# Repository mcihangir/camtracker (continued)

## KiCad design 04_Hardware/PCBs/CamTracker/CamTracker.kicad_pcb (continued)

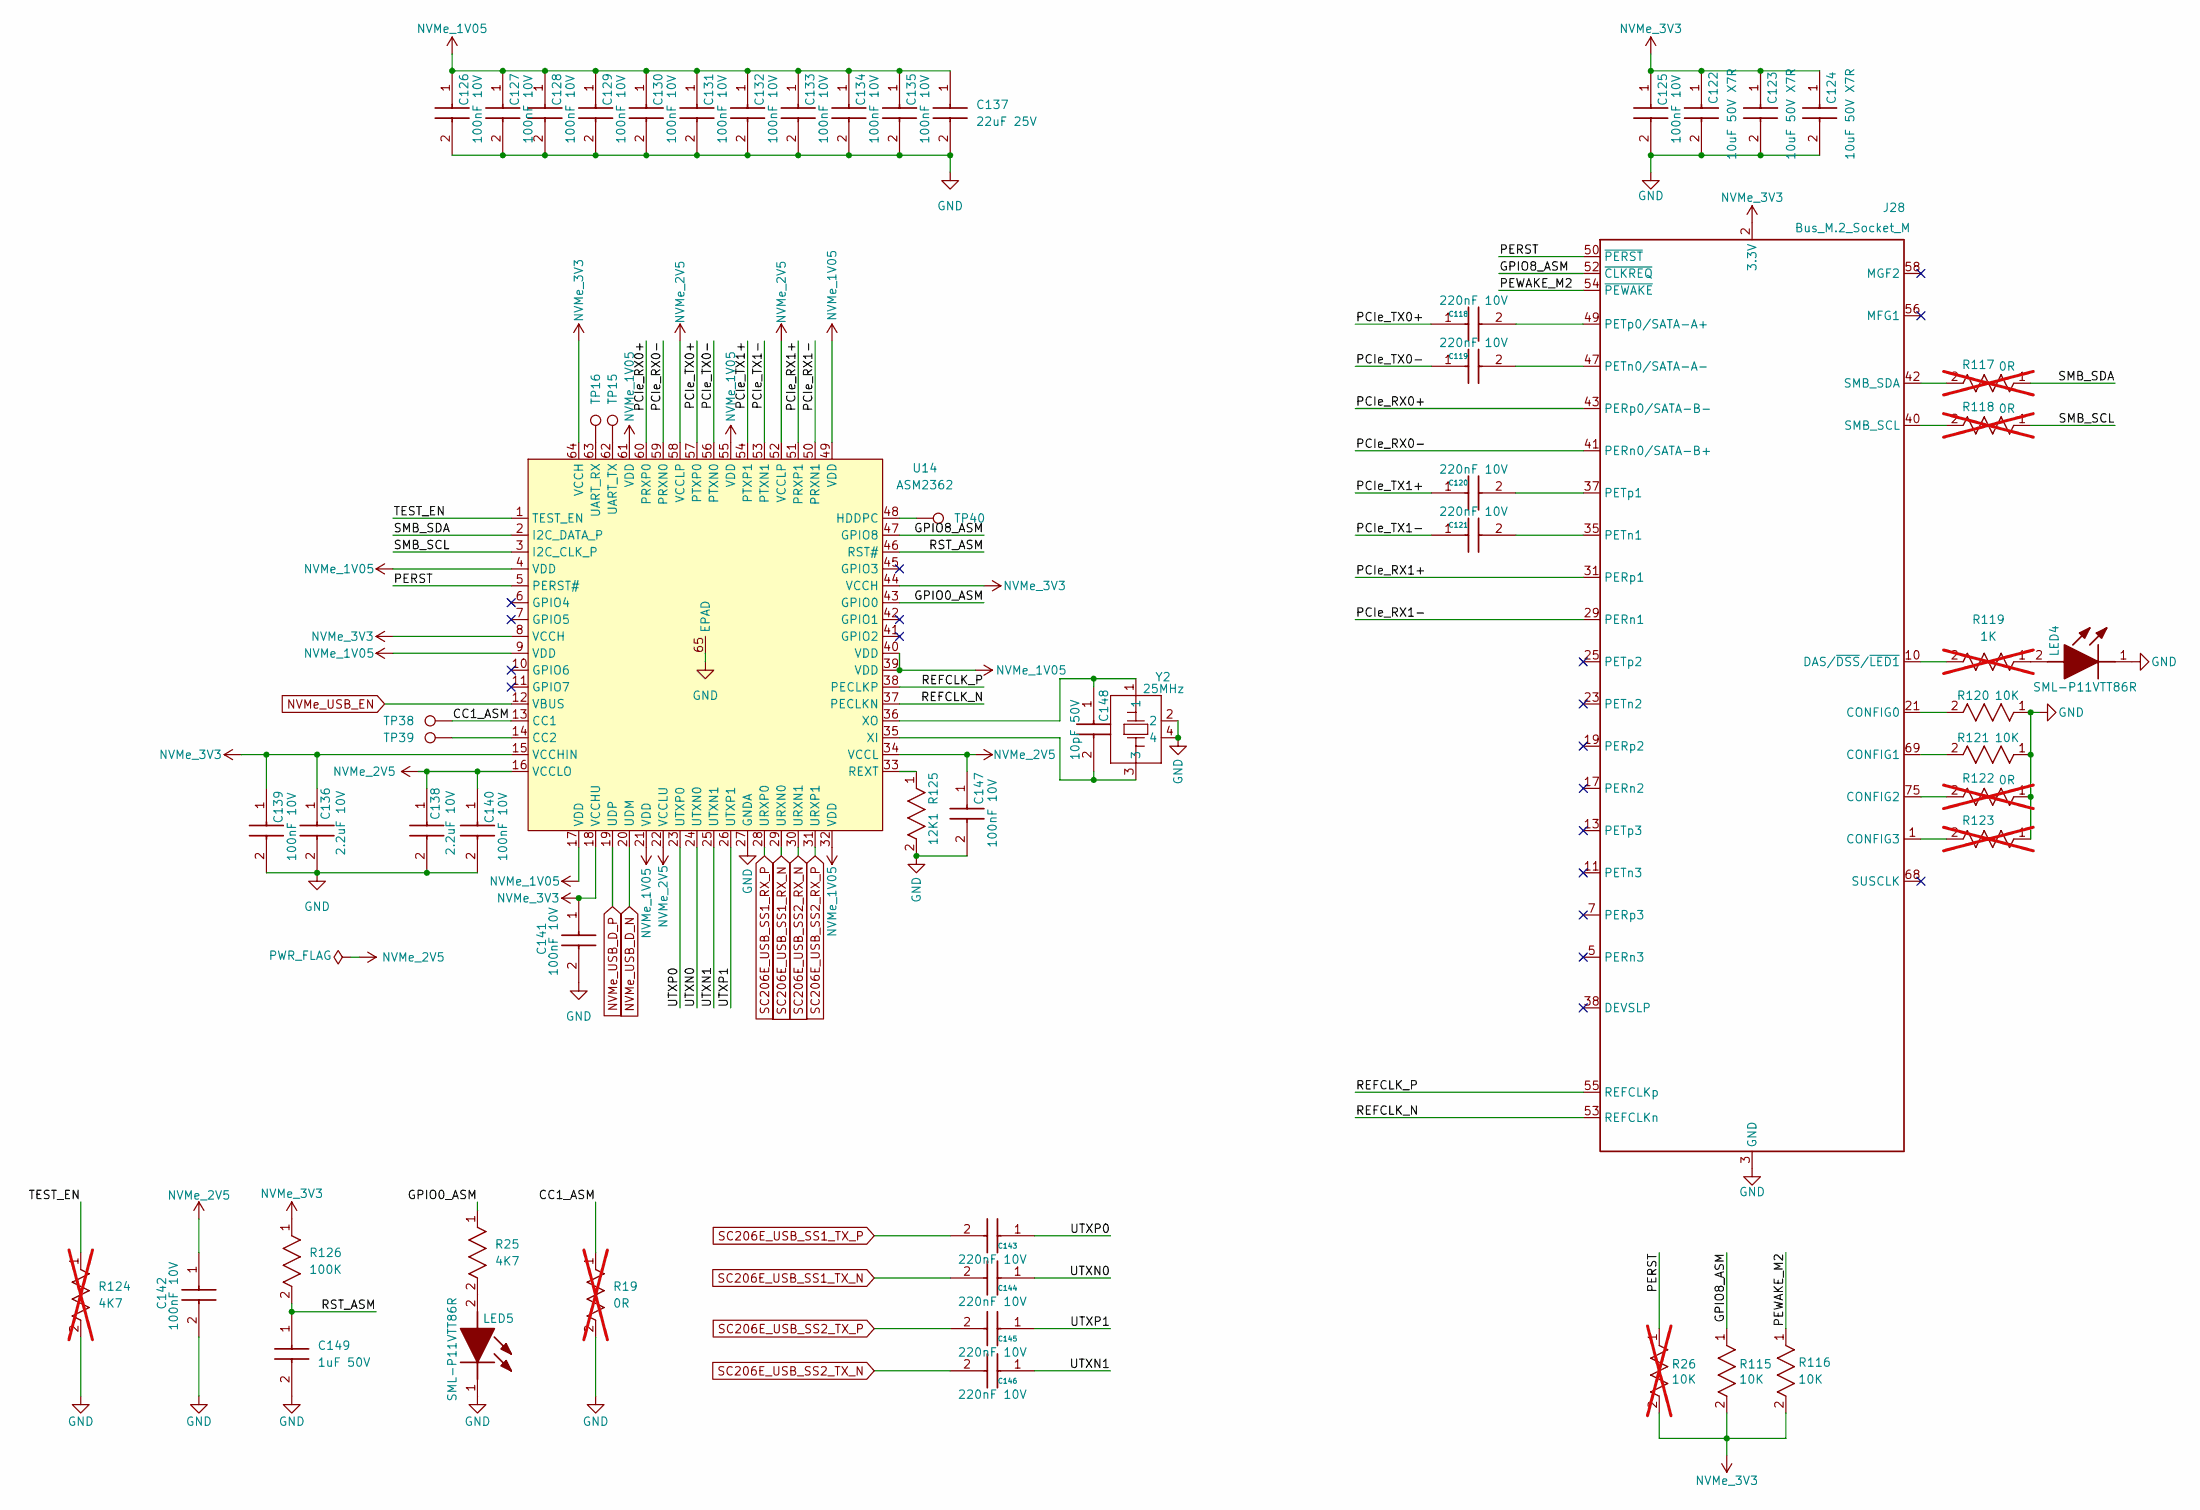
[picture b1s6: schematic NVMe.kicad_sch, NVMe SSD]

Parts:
C118, C119, C120, C121, C143, C144, C145, C146: 220nF 10V; CAPC1005X55N; Part Number GRM155R61A224JE19D
C122, C123, C124: 10uF 50V X7R; CAPC3216X190N; Part Number CL31B106KBK6PJE
C125, C126, C127, C128, C129, C130, C131, C132, C133, C134, C135, C139, C140, C141, C142, C147: 100nF 10V; CAPC1005X55N; Part Number GRM155R71A104KA01D
C136, C138: 2.2uF 10V; CAPC1608X90N; Part Number LMK107BJ225KA-T
C137: 22uF 25V; CAPC2012X145N; Part Number GRM21BR61E226ME44L
C148: 10pF 50V; CAPC1005X55N; Part Number GRM1555C1H100JA01D
C149: 1uF 50V; CAPC1005X55N; Part Number GRM155R61H105KE05D
J28: Bus_M.2_Socket_M; NVMEE; Part Number 1-2199230-4
LED4, LED5: SML-P11VTT86R; SMLP11VTT86R; Part Number SML-P11VTT86R
R19: 0R; RESC2012X50N; Part Number CRCW08050000Z0EA; not fitted
R25: 4K7; RC0402N_YAG; Part Number RC0402JR-074K7L
R26: 10K; RC0402N_YAG; Part Number RC0402JR-0710KL; not fitted
R115, R116, R120, R121: 10K; RC0402N_YAG; Part Number RC0402JR-0710KL
R117, R118, R122, R123: 0R; RC0402N_YAG; Part Number RC0402JR-070RL; not fitted
R119: 1K; RC0402N_YAG; Part Number RC0402JR-071KL; not fitted
R124: 4K7; RC0402N_YAG; Part Number RC0402JR-074K7L; not fitted
R125: 12K1; RC0402N_YAG; Part Number RC0402FR-0712K1P
R126: 100K; RC0402N_YAG; Part Number RC0402JR-07100KL
TP15, TP16, TP38, TP39, TP40: 3.86V; TestPoint_Pad_D1.0mm
U14: ASM2362; QFN50P905X905X75-65N; Part Number ASM2362
Y2: 25MHz; FL2500188; Part Number FL2500188

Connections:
/NVMe/CC1_ASM: R19.1, TP38.1, U14.13 (CC1)
/NVMe/GPIO0_ASM: R25.1, U14.43 (GPIO0)
/NVMe/GPIO8_ASM: J28.52 (~CLKREQ), R115.1, U14.47 (GPIO8)
/NVMe/PCIe_RX0+: J28.43 (PERp0/SATA-B-), U14.60 (PRXP0)
/NVMe/PCIe_RX0-: J28.41 (PERn0/SATA-B+), U14.59 (PRXN0)
/NVMe/PCIe_RX1+: J28.31 (PERp1), U14.51 (PRXP1)
/NVMe/PCIe_RX1-: J28.29 (PERn1), U14.50 (PRXN1)
/NVMe/PCIe_TX0+: C118.1, U14.57 (PTXP0)
/NVMe/PCIe_TX0-: C119.1, U14.56 (PTXN0)
/NVMe/PCIe_TX1+: C120.1, U14.54 (PTXP1)
/NVMe/PCIe_TX1-: C121.1, U14.53 (PTXN1)
/NVMe/PERST: J28.50 (~PERST), R26.1, U14.5 (PERST#)
/NVMe/PEWAKE_M2: J28.54 (~PEWAKE), R116.1
/NVMe/REFCLK_N: J28.53 (REFCLKn), U14.37 (PECLKN)
/NVMe/REFCLK_P: J28.55 (REFCLKp), U14.38 (PECLKP)
/NVMe/RST_ASM: C149.1, R126.2, U14.46 (RST#)
/NVMe/SMB_SCL: R118.1, U14.3 (I2C_CLK_P)
/NVMe/SMB_SDA: R117.1, U14.2 (I2C_DATA_P)
/NVMe/TEST_EN: R124.1, U14.1 (TEST_EN)
/NVMe/UTXN0: C144.1, U14.24 (UTXN0)
/NVMe/UTXN1: C146.1, U14.25 (UTXN1)
/NVMe/UTXP0: C143.1, U14.23 (UTXP0)
/NVMe/UTXP1: C145.1, U14.26 (UTXP1)
GND: C122.2, C123.2, C124.2, C125.2, C126.2, C127.2, C128.2, C129.2, C130.2, C131.2, C132.2, C133.2, C134.2, C135.2, C136.2, C137.2, C138.2, C139.2, C140.2, C141.2, C142.2, C147.2, C149.2, J28.0 (GND), J28.3 (GND), J28.9 (GND), J28.15 (GND), J28.27 (GND), J28.33 (GND), J28.39 (GND), J28.45 (GND), J28.51 (GND), J28.57 (GND), J28.71 (GND), J28.73 (GND), J28.76 (GND), J28.77 (GND), LED4.1 (K), LED5.1 (K), R19.2, R120.1, R121.1, R122.1, R123.1, R124.2, R125.2, U14.27 (GNDA), U14.65 (EPAD), Y2.2, Y2.4; also elsewhere on the board
NVMe_1V05: C126.1, C127.1, C128.1, C129.1, C130.1, C131.1, C132.1, C133.1, C134.1, C135.1, C137.1, U14.4 (VDD), U14.9 (VDD), U14.17 (VDD), U14.21 (VDD), U14.32 (VDD), U14.39 (VDD), U14.40 (VDD), U14.49 (VDD), U14.55 (VDD), U14.61 (VDD); also elsewhere on the board
NVMe_2V5: C138.1, C140.1, C142.1, C147.1, U14.16 (VCCLO), U14.22 (VCCLU), U14.34 (VCCL), U14.52 (VCCLP), U14.58 (VCCLP)
NVMe_3V3: C122.1, C123.1, C124.1, C125.1, C136.1, C139.1, C141.1, J28.2 (3.3V), J28.4 (3.3V), J28.12 (3.3V), J28.14 (3.3V), J28.16 (3.3V), J28.18 (3.3V), J28.70 (3.3V), J28.72 (3.3V), J28.74 (3.3V), R26.2, R115.2, R116.2, R126.1, U14.8 (VCCH), U14.15 (VCCHIN), U14.18 (VCCHU), U14.44 (VCCH), U14.64 (VCCH); also elsewhere on the board
NVMe_USB_D_N: U14.20 (UDM); also elsewhere on the board
NVMe_USB_D_P: U14.19 (UDP); also elsewhere on the board
NVMe_USB_EN: U14.12 (VBUS); also elsewhere on the board
unnamed: J28.21 (CONFIG0), R120.2
unnamed: J28.69 (CONFIG1), R121.2
unnamed: J28.75 (CONFIG2), R122.2
unnamed: J28.1 (CONFIG3), R123.2
unnamed: J28.10 (DAS/~DSS/~LED1), R119.2
unnamed: C119.2, J28.47 (PETn0/SATA-A-)
unnamed: C121.2, J28.35 (PETn1)
unnamed: C118.2, J28.49 (PETp0/SATA-A+)
unnamed: C120.2, J28.37 (PETp1)
unnamed: J28.40 (SMB_SCL), R118.2
unnamed: J28.42 (SMB_SDA), R117.2
unnamed: LED4.2 (A), R119.1
unnamed: LED5.2 (A), R25.2
unnamed: TP39.1, U14.14 (CC2)
unnamed: TP40.1, U14.48 (HDDPC)
unnamed: R125.1, U14.33 (REXT)
unnamed: TP16.1, U14.63 (UART_RX)
unnamed: TP15.1, U14.62 (UART_TX)
unnamed: C148.2, U14.35 (XI), Y2.3
unnamed: C148.1, U14.36 (XO), Y2.1
SC206E_USB_SS1_RX_N: U14.29 (URXN0); also elsewhere on the board
SC206E_USB_SS1_RX_P: U14.28 (URXP0); also elsewhere on the board
SC206E_USB_SS1_TX_N: C144.2; also elsewhere on the board
SC206E_USB_SS1_TX_P: C143.2; also elsewhere on the board
SC206E_USB_SS2_RX_N: U14.30 (URXN1); also elsewhere on the board
SC206E_USB_SS2_RX_P: U14.31 (URXP1); also elsewhere on the board
SC206E_USB_SS2_TX_N: C146.2; also elsewhere on the board
SC206E_USB_SS2_TX_P: C145.2; also elsewhere on the board

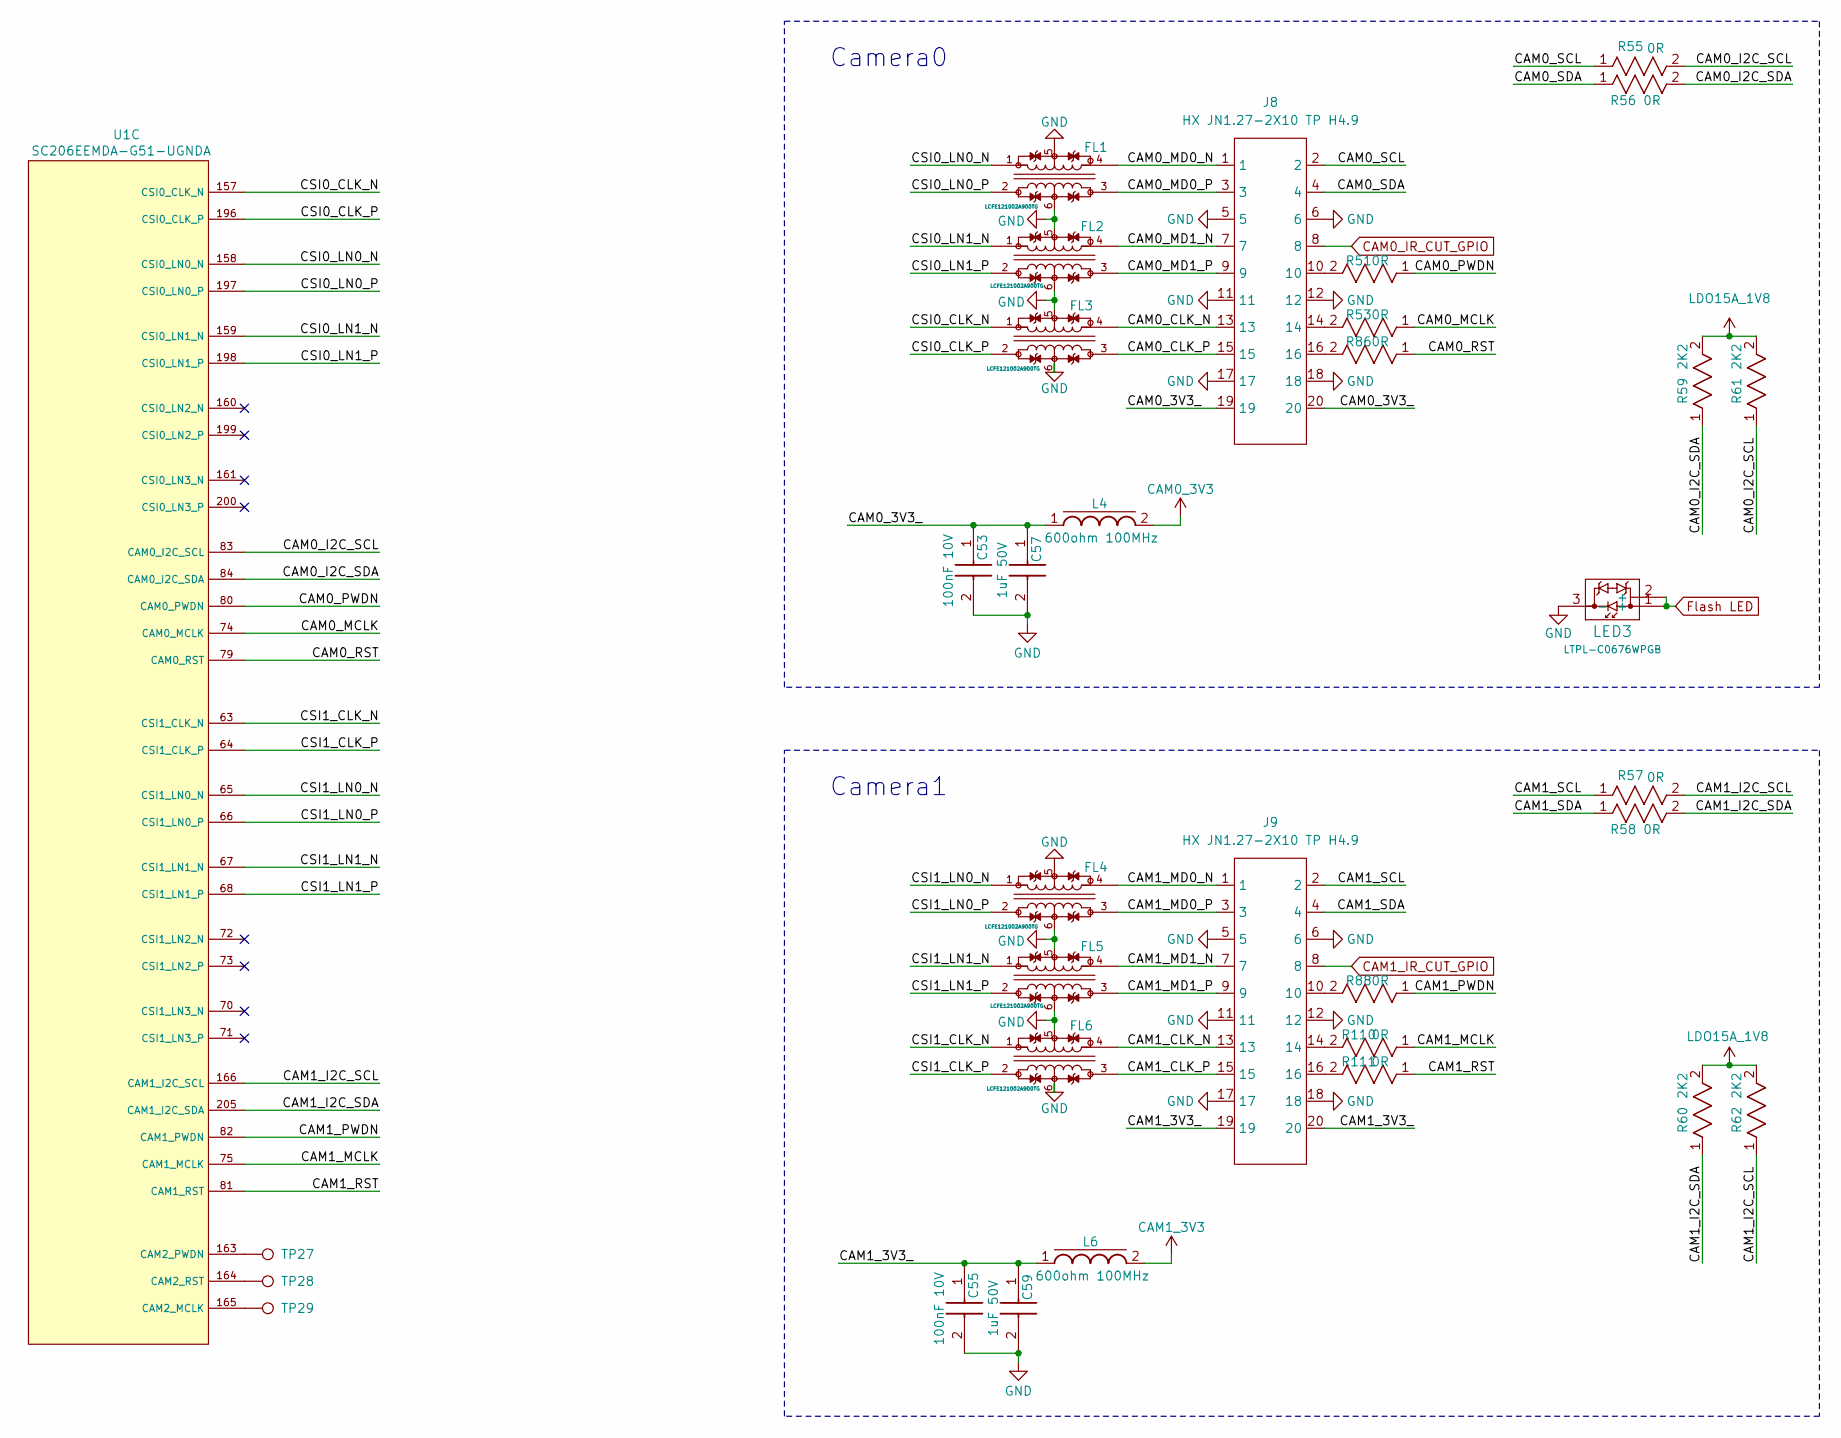
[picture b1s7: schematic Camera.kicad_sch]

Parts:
C53, C55: 100nF 10V; CAPC1005X55N; Part Number GRM155R71A104KA01D
C57, C59: 1uF 50V; CAPC1005X55N; Part Number GRM155R61H105KE05D
FL1, FL2, FL3, FL4, FL5, FL6: LCFE121002A900TG; Part Number LCFE121002A900TG
J8, J9: HX JN1.27-2X10 TP H4.9; CONN-SMD_HX-JN1.27-2X10-TP-H4.9; Part Number HX JN1.27-2x10 TP H4.9
L4, L6: 600ohm 100MHz; 0402; Part Number 7427927291
LED3: LTPL-C0676WPGB; Part Number LTPL-C0676WPGB
R51, R53, R86, R88, R110, R111: 0R; RC0402N_YAG; Part Number RC0402JR-070RL
R55, R56, R57, R58: 0R; RESC2012X50N; Part Number CRCW08050000Z0EA
R59, R60, R61, R62: 2K2; RC0402N_YAG; Part Number RC0402JR-072K2L
TP27, TP28, TP29: TestPoint; TestPoint_Pad_D1.0mm
U1: SC206EEMDA-G51-UGNDA; SC200E_SC206E; Part Number SC200EEMNA-E53-UGNDA

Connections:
/Cameras/CAM0_3V3_: C53.1, C57.1, J8.19, J8.20, L4.1
/Cameras/CAM0_CLK_N: FL3.4, J8.13
/Cameras/CAM0_CLK_P: FL3.3, J8.15
/Cameras/CAM0_I2C_SCL: R55.2, R61.1, U1.83 (CAM0_I2C_SCL)
/Cameras/CAM0_I2C_SDA: R56.2, R59.1, U1.84 (CAM0_I2C_SDA)
/Cameras/CAM0_MCLK: R53.1, U1.74 (CAM0_MCLK)
/Cameras/CAM0_MD0_N: FL1.4, J8.1
/Cameras/CAM0_MD0_P: FL1.3, J8.3
/Cameras/CAM0_MD1_N: FL2.4, J8.7
/Cameras/CAM0_MD1_P: FL2.3, J8.9
/Cameras/CAM0_PWDN: R51.1, U1.80 (CAM0_PWDN)
/Cameras/CAM0_RST: R86.1, U1.79 (CAM0_RST)
/Cameras/CAM0_SCL: J8.2, R55.1
/Cameras/CAM0_SDA: J8.4, R56.1
/Cameras/CAM1_3V3_: C55.1, C59.1, J9.19, J9.20, L6.1
/Cameras/CAM1_CLK_N: FL6.4, J9.13
/Cameras/CAM1_CLK_P: FL6.3, J9.15
/Cameras/CAM1_I2C_SCL: R57.2, R62.1, U1.166 (CAM1_I2C_SCL)
/Cameras/CAM1_I2C_SDA: R58.2, R60.1, U1.205 (CAM1_I2C_SDA)
/Cameras/CAM1_MCLK: R110.1, U1.75 (CAM1_MCLK)
/Cameras/CAM1_MD0_N: FL4.4, J9.1
/Cameras/CAM1_MD0_P: FL4.3, J9.3
/Cameras/CAM1_MD1_N: FL5.4, J9.7
/Cameras/CAM1_MD1_P: FL5.3, J9.9
/Cameras/CAM1_PWDN: R88.1, U1.82 (CAM1_PWDN)
/Cameras/CAM1_RST: R111.1, U1.81 (CAM1_RST)
/Cameras/CAM1_SCL: J9.2, R57.1
/Cameras/CAM1_SDA: J9.4, R58.1
/Cameras/CSI0_CLK_N: FL3.1, U1.157 (CSI0_CLK_N)
/Cameras/CSI0_CLK_P: FL3.2, U1.196 (CSI0_CLK_P)
/Cameras/CSI0_LN0_N: FL1.1, U1.158 (CSI0_LN0_N)
/Cameras/CSI0_LN0_P: FL1.2, U1.197 (CSI0_LN0_P)
/Cameras/CSI0_LN1_N: FL2.1, U1.159 (CSI0_LN1_N)
/Cameras/CSI0_LN1_P: FL2.2, U1.198 (CSI0_LN1_P)
/Cameras/CSI1_CLK_N: FL6.1, U1.63 (CSI1_CLK_N)
/Cameras/CSI1_CLK_P: FL6.2, U1.64 (CSI1_CLK_P)
/Cameras/CSI1_LN0_N: FL4.1, U1.65 (CSI1_LN0_N)
/Cameras/CSI1_LN0_P: FL4.2, U1.66 (CSI1_LN0_P)
/Cameras/CSI1_LN1_N: FL5.1, U1.67 (CSI1_LN1_N)
/Cameras/CSI1_LN1_P: FL5.2, U1.68 (CSI1_LN1_P)
CAM0_3V3: L4.2; also elsewhere on the board
CAM0_IR_CUT_GPIO: J8.8; also elsewhere on the board
CAM1_3V3: L6.2; also elsewhere on the board
CAM1_IR_CUT_GPIO: J9.8; also elsewhere on the board
Flash LED: LED3.1 (+), LED3.2 (+); also elsewhere on the board
GND: C53.2, C55.2, C57.2, C59.2, FL1.5, FL1.6, FL2.5, FL2.6, FL3.5, FL3.6, FL4.5, FL4.6, FL5.5, FL5.6, FL6.5, FL6.6, J8.5, J8.6, J8.11, J8.12, J8.17, J8.18, J9.5, J9.6, J9.11, J9.12, J9.17, J9.18, LED3.3 (-); also elsewhere on the board
LDO15A_1V8: R59.2, R60.2, R61.2, R62.2; also elsewhere on the board
unnamed: J8.10, R51.2
unnamed: J8.14, R53.2
unnamed: J8.16, R86.2
unnamed: J9.10, R88.2
unnamed: J9.14, R110.2
unnamed: J9.16, R111.2
unnamed: TP29.1, U1.165 (CAM2_MCLK)
unnamed: TP27.1, U1.163 (CAM2_PWDN)
unnamed: TP28.1, U1.164 (CAM2_RST)

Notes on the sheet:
Camera0
Camera1

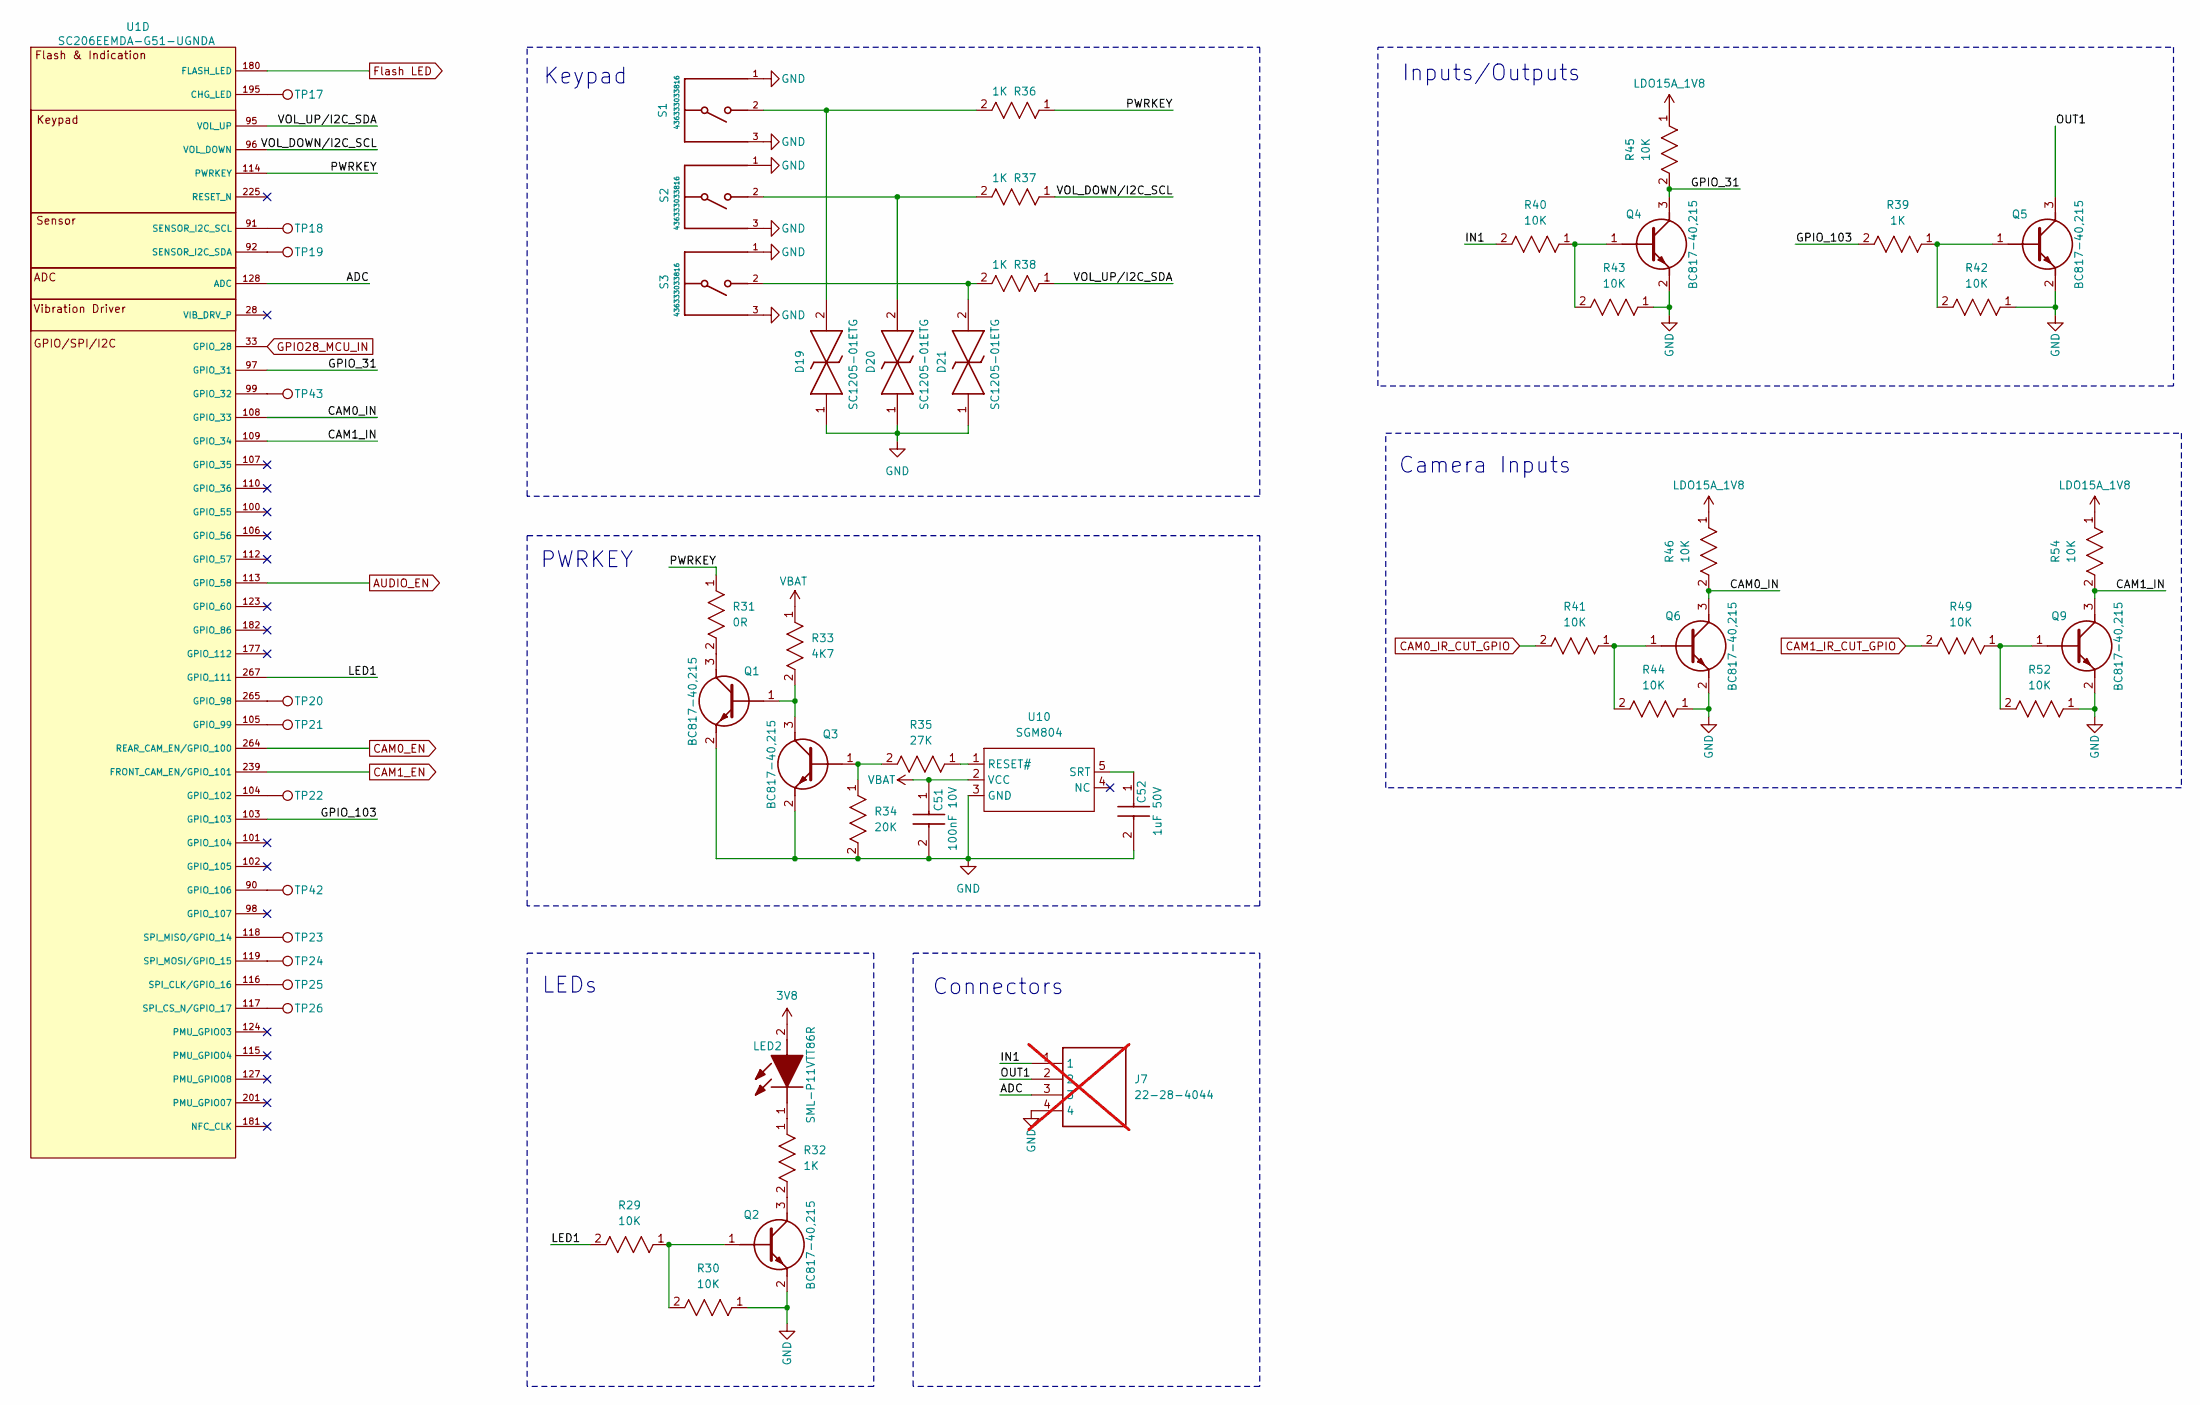
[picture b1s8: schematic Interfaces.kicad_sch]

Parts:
C51: 100nF 10V; CAPC1005X55N; Part Number GRM155R71A104KA01D
C52: 1uF 50V; CAPC1005X55N; Part Number GRM155R61H105KE05D
D19, D20, D21: SC1205-01ETG; SC120501ETG; Part Number SC1205-01ETG
J7: 22-28-4044; HDRV3W66P0X254_1X4_762X249X1042P; Part Number 22-28-4044; not fitted
LED2: SML-P11VTT86R; SMLP11VTT86R; Part Number SML-P11VTT86R
Q1, Q2, Q3, Q4, Q5, Q6, Q9: BC817-40,215; BC81740215; Part Number BC817-40,215
R29, R30, R40, R41, R42, R43, R44, R45, R46, R49, R52, R54: 10K; RC0402N_YAG; Part Number RC0402JR-0710KL
R31: 0R; RESC2012X50N; Part Number CRCW08050000Z0EA
R32, R36, R37, R38, R39: 1K; RC0402N_YAG; Part Number RC0402JR-071KL
R33: 4K7; RC0402N_YAG; Part Number RC0402JR-074K7L
R34: 20K; RC0402N_YAG; Part Number RC0402JR-0720KL
R35: 27K; RC0402N_YAG; Part Number RC0402JR-0727KL
S1, S2, S3: 436333033816; Part Number 436333033816
TP17, TP18, TP19, TP20, TP21, TP22, TP23, TP24, TP25, TP26, TP42, TP43: TestPoint; TestPoint_Pad_D1.0mm
U1: SC206EEMDA-G51-UGNDA; SC200E_SC206E; Part Number SC200EEMNA-E53-UGNDA
U10: SGM804; SOT-23-5_L2.9-W1.6-P0.95-LS2.8-BL; Part Number SGM804-2.93YN5G/TR

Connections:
3V8: LED2.2 (A); also elsewhere on the board
/Interfaces/ADC: J7.3, U1.128 (ADC)
/Interfaces/CAM0_IN: Q6.3 (C), R46.2, U1.108 (GPIO_33)
/Interfaces/CAM1_IN: Q9.3 (C), R54.2, U1.109 (GPIO_34)
/Interfaces/GPIO_31: Q4.3 (C), R45.2, U1.97 (GPIO_31)
/Interfaces/GPIO_103: R39.2, U1.103 (GPIO_103)
/Interfaces/IN1: J7.1, R40.2
/Interfaces/LED1: R29.2, U1.267 (GPIO_111)
/Interfaces/OUT1: J7.2, Q5.3 (C)
/Interfaces/PWRKEY: R31.1, R36.1, U1.114 (PWRKEY)
/Interfaces/VOL_DOWN/I2C_SCL: R37.1, U1.96 (VOL_DOWN)
/Interfaces/VOL_UP/I2C_SDA: R38.1, U1.95 (VOL_UP)
AUDIO_EN: U1.113 (GPIO_58); also elsewhere on the board
CAM0_EN: U1.264 (REAR_CAM_EN/GPIO_100); also elsewhere on the board
CAM0_IR_CUT_GPIO: R41.2; also elsewhere on the board
CAM1_EN: U1.239 (FRONT_CAM_EN/GPIO_101); also elsewhere on the board
CAM1_IR_CUT_GPIO: R49.2; also elsewhere on the board
Flash LED: U1.180 (FLASH_LED); also elsewhere on the board
GND: C51.2, C52.2, D19.1, D20.1, D21.1, J7.4, Q1.2 (E), Q2.2 (E), Q3.2 (E), Q4.2 (E), Q5.2 (E), Q6.2 (E), Q9.2 (E), R30.1, R34.2, R42.1, R43.1, R44.1, R52.1, S1.1, S1.3, S2.1, S2.3, S3.1, S3.3, U10.3 (GND); also elsewhere on the board
GPIO28_MCU_IN: U1.33 (GPIO_28); also elsewhere on the board
LDO15A_1V8: R45.1, R46.1, R54.1; also elsewhere on the board
unnamed: D19.2, R36.2, S1.2
unnamed: D20.2, R37.2, S2.2
unnamed: D21.2, R38.2, S3.2
unnamed: LED2.1 (K), R32.1
unnamed: Q1.1 (B), Q3.3 (C), R33.2
unnamed: Q1.3 (C), R31.2
unnamed: Q2.1 (B), R29.1, R30.2
unnamed: Q2.3 (C), R32.2
unnamed: Q3.1 (B), R34.1, R35.2
unnamed: Q4.1 (B), R40.1, R43.2
unnamed: Q5.1 (B), R39.1, R42.2
unnamed: Q6.1 (B), R41.1, R44.2
unnamed: Q9.1 (B), R49.1, R52.2
unnamed: TP17.1, U1.195 (CHG_LED)
unnamed: TP43.1, U1.99 (GPIO_32)
unnamed: TP20.1, U1.265 (GPIO_98)
unnamed: TP21.1, U1.105 (GPIO_99)
unnamed: TP22.1, U1.104 (GPIO_102)
unnamed: TP42.1, U1.90 (GPIO_106)
unnamed: TP18.1, U1.91 (SENSOR_I2C_SCL)
unnamed: TP19.1, U1.92 (SENSOR_I2C_SDA)
unnamed: TP25.1, U1.116 (SPI_CLK/GPIO_16)
unnamed: TP26.1, U1.117 (SPI_CS_N/GPIO_17)
unnamed: TP23.1, U1.118 (SPI_MISO/GPIO_14)
unnamed: TP24.1, U1.119 (SPI_MOSI/GPIO_15)
unnamed: R35.1, U10.1 (RESET#)
unnamed: C52.1, U10.5 (SRT)
VBAT: C51.1, R33.1, U10.2 (VCC); also elsewhere on the board

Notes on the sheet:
Inputs/Outputs
LEDs
PWRKEY
Keypad
Camera Inputs
Connectors

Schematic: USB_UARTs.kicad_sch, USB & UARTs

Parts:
C31, C35, C41, C112, C113: 1uF 50V; CAPC1005X55N; Part Number GRM155R61H105KE05D
C32, C40, C111: 100nF 10V; CAPC1005X55N; Part Number GRM155R71A104KA01D
C38: 10nF 50V; CAPC1005X55N; Part Number GRM155R71H103KA88D
C42: 4.7uF 10V; CAPC1608X90N; Part Number LMK107BJ475KA-T
D1: 1N4148WS; SODFL2512X90N; Part Number 1N4148WS
D9: SC1205-01ETG; SC120501ETG; Part Number SC1205-01ETG
D11, D18: SP0402U-ULC-02ETG; SESD0402Q2UG0020090; Part Number SP0402U-ULC-02ETG
D12: SC1105-01UTG; SC110501UTG; Part Number SC1105-01UTG
J3: 67996-100HLF; HDRV2W67P254_2X1_254X483X858P; Part Number 67996-100HLF
J5: 22-28-4034; HDRV3W66P0X254_1X3_762X249X1042P; Part Number 22-28-4034
J6: 2345986-1; TE_2345986-1; Part Number 2345986-1
Q7: BC817-40,215; BC81740215; Part Number BC817-40,215
R20: 0R; RESC2012X50N; Part Number CRCW08050000Z0EA; not fitted
R21, R24: 10K; RC0402N_YAG; Part Number RC0402JR-0710KL
R22: 100K; RC0402N_YAG; Part Number RC0402JR-07100KL
R23: 10K; RC0402N_YAG; Part Number RC0402JR-0710KL; not fitted
R104: 56K; RC0402N_YAG; Part Number RC0402JR-0756KL
R109: 5K1; RC0402N_YAG; Part Number RC0402JR-075K1L
R112: 0R; RESC2012X50N; Part Number CRCW08050000Z0EA
S4: JS102011JCQN; SW_JS102011JCQN; Part Number JS102011JCQN
TP12, TP13, TP14, TP44, TP45, TP50, TP51: TestPoint; TestPoint_Pad_D1.0mm
U1: SC206EEMDA-G51-UGNDA; SC200E_SC206E; Part Number SC200EEMNA-E53-UGNDA
U7, U9: PI3USB4000DZUAEX; Part Number PI3USB4000DZUAEX

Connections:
3V8: C31.1, C32.1, C111.1, C112.1, U7.10 (VDD), U9.10 (VDD); also elsewhere on the board
/USB_UARTs/SC206E_CC1: U1.249 (USB_CC1), U9.8 (C0+)
/USB_UARTs/SC206E_USB_D_N: U1.13 (USB_DM), U7.7 (C0-)
/USB_UARTs/SC206E_USB_D_P: U1.14 (USB_DP), U7.8 (C0+)
/USB_UARTs/TypeC_USB_D_N: D18.1 (K_1), J6.A7 (DN1), J6.B7 (DN2), U7.4 (L1-)
/USB_UARTs/TypeC_USB_D_P: D18.2 (K_2), J6.A6 (DP1), J6.B6 (DP2), U7.3 (L1+)
/USB_UARTs/USB_SW: C38.1, R22.1, R112.1, S4.3, TP51.1, U7.9 (SEL), U9.9 (SEL)
GND: C31.2, C32.2, C35.2, C38.2, C40.2, C41.2, C42.2, C111.2, C112.2, C113.2, D9.2, D11.3 (GND), D12.2 (A), D18.3 (GND), J5.3, J6.A1 (GND_A), J6.A12 (GND_A__1), J6.B1 (GND_B), J6.B12 (GND_B__1), J6.SH1 (SHIELD), J6.SH2 (SHIELD__1), J6.SH3 (SHIELD__2), J6.SH4 (SHIELD__3), Q7.2 (E), R22.2, R109.2, U7.5 (GND), U9.5 (GND); also elsewhere on the board
LDO15A_1V8: R23.1, R24.2; also elsewhere on the board
NVMe_USB_D_N: U7.2 (L0-); also elsewhere on the board
NVMe_USB_D_P: U7.1 (L0+); also elsewhere on the board
NVMe_USB_EN: Q7.3 (C), TP50.1; also elsewhere on the board
unnamed: D11.1 (K_1), J5.2, R23.2, U1.93 (DBG_UART4_RXD)
unnamed: D11.2 (K_2), J5.1, U1.94 (DBG_UART4_TXD)
unnamed: J3.2, R24.1
unnamed: Q7.1 (B), R112.2
unnamed: R21.2, S4.2
unnamed: TP12.1, U1.36 (UART0_CTS/I2C_SDA)
unnamed: TP13.1, U1.37 (UART0_RTS/I2C_SCL)
unnamed: TP45.1, U1.153 (UART1_RXD)
unnamed: TP44.1, U1.154 (UART1_TXD)
unnamed: D9.1, J3.1, U1.46 (USB_BOOT)
unnamed: R20.1, U1.246 (USB_CC2)
unnamed: C35.1, U7.6 (REF)
unnamed: R109.1, U9.1 (L0+)
unnamed: R104.1, U9.3 (L1+)
unnamed: C113.1, U9.6 (REF)
SC206E_USB_SS1_RX_N: U1.270 (USB_SS1_RX_M); also elsewhere on the board
SC206E_USB_SS1_RX_P: U1.252 (USB_SS1_RX_P); also elsewhere on the board
SC206E_USB_SS1_TX_N: U1.253 (USB_SS1_TX_M); also elsewhere on the board
SC206E_USB_SS1_TX_P: U1.254 (USB_SS1_TX_P); also elsewhere on the board
SC206E_USB_SS2_RX_N: U1.192 (USB_SS2_RX_M); also elsewhere on the board
SC206E_USB_SS2_RX_P: U1.152 (USB_SS2_RX_P); also elsewhere on the board
SC206E_USB_SS2_TX_N: U1.151 (USB_SS2_TX_M); also elsewhere on the board
SC206E_USB_SS2_TX_P: U1.150 (USB_SS2_TX_P); also elsewhere on the board
TypeC_VBUS: D1.2 (A), J6.A4 (VBUS_A), J6.A9 (VBUS_A__1), J6.B4 (VBUS_B), J6.B9 (VBUS_B__1), R21.1, R104.2; also elsewhere on the board
UART0_RXD: U1.35 (UART0_RXD/GPIO_3); also elsewhere on the board
UART0_TXD: U1.34 (UART0_TXD/GPIO_2); also elsewhere on the board
VUSB_BUS: C40.1, C41.1, C42.1, D1.1 (K), D12.1 (K), TP14.1, U1.141 (USB_VBUS), U1.142 (USB_VBUS)

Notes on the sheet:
CC1=5K1 Pull-down ==> SC206 Host CC1=56K Pull-up ==> SC206 Device
USB Switches
Operation mode Select (when SEL=0: C0→L0, when SEL=1: C0→L1)
Type-C
Debug UART

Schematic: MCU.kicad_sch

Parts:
C82, C83: 15pF 50V; CAPC1005X55N; Part Number GRM1555C1H150JA01D
C84, C85, C88, C89, C90, C91, C92, C93, C94, C95: 100nF 10V; CAPC1005X55N; Part Number GRM155R71A104KA01D
C86, C87: 1uF 50V; CAPC1005X55N; Part Number GRM155R61H105KE05D
C96, C97: 1nF 50V; CAPC1005X55N; Part Number GRM1555C1H102JA01D
IC1: W25Q128JVSIM; SOIC127P790X216-8N; Part Number W25Q128JVSIM
J4: CONN-SMD_1.25-4PLT; Part Number 1.25-4P LT
J19: 2174507-2; 21745072; Part Number 2174507-2
J21: 67996-100HLF; HDRV2W67P254_2X1_254X483X858P; Part Number 67996-100HLF
J23, J26: CONN-SMD_1.25-4PLT; Part Number 1.25-4P LT; not fitted
Q8, Q10, Q11: BC817-40,215; BC81740215; Part Number BC817-40,215
R28, R47, R48, R97, R98: 10K; RC0402N_YAG; Part Number RC0402JR-0710KL
R50: 0R; RESC2012X50N; Part Number CRCW08050000Z0EA
R91, R95: 1K; RC0402N_YAG; Part Number RC0402JR-071KL
R92: 10K; RC0402N_YAG; Part Number RC0402JR-0710KL; not fitted
R93, R94: 27.4R; RC0402N_YAG; Part Number RC0402FR-0727R4P
R96, R99: 4K7; RC0402N_YAG; Part Number RC0402JR-074K7L
TP33, TP34, TP35, TP36, TP46, TP47, TP48, TP49: TestPoint; TestPoint_Pad_D1.0mm
U12: RP2040; QFN40P700X700X90-57N-D; Part Number SC0914(7)
Y1: ABM8-272-T3; ABM8272T3; Part Number ABM8-272-T3

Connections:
/MCU/ADC0: J26.1, U12.38 (GPIO26_ADC0)
/MCU/ADC1: J26.2, U12.39 (GPIO27_ADC1)
/MCU/ADC2: J26.3, U12.40 (GPIO28_ADC2)
/MCU/ADC3: J26.4, U12.41 (GPIO29_ADC3)
/MCU/GPIO4: J23.1, U12.6 (GPIO4)
/MCU/GPIO5: J23.2, U12.7 (GPIO5)
/MCU/GPIO6: J23.3, U12.8 (GPIO6)
/MCU/GPIO7: J23.4, U12.9 (GPIO7)
/MCU/MCU_OUT: R28.2, U12.37 (GPIO25)
/MCU/MCU_UART_RX: Q11.3 (C), R98.2, U12.3 (GPIO1)
/MCU/MCU_UART_TX: Q10.2 (E), U12.2 (GPIO0)
/MCU/MCU_USB_N: R94.1, U12.46 (USB_DM)
/MCU/MCU_USB_P: R93.1, U12.47 (USB_DP)
/MCU/QSPI_SCLK: IC1.6 (CLK), U12.52 (QSPI_SCLK)
/MCU/QSPI_SD0: IC1.5 (DI_(IO0)), U12.53 (QSPI_SD0)
/MCU/QSPI_SD1: IC1.2 (DO_(IO1)), U12.55 (QSPI_SD1)
/MCU/QSPI_SD2: IC1.3 (~WP_(IO2)), U12.54 (QSPI_SD2)
/MCU/QSPI_SD3: IC1.7 (~HOLD_OR_/RESET_(IO3)), U12.51 (QSPI_SD3)
/MCU/QSPI_SS: IC1.1 (~CS), R91.1, R92.2, U12.56 (QSPI_SS)
/MCU/RUN: J4.4, U12.26 (RUN)
/MCU/SWCLK: J4.1, U12.24 (SWCLK)
/MCU/SWD: J4.2, U12.25 (SWD)
/MCU/USB_BOOT: J21.2, R91.2
GND: C82.2, C83.2, C84.2, C85.2, C86.2, C87.2, C88.2, C89.2, C90.2, C91.2, C92.2, C93.2, C94.2, C95.2, IC1.4 (GND), J4.3, J4.5, J4.6, J19.5, J19.MP1, J19.MP2, J19.MP3, J19.MP4, J19.MP5, J19.MP6, J21.1, J23.5, J23.6, J26.5, J26.6, Q8.2 (E), R47.1, U12.19 (TESTEN), U12.57 (GND), Y1.2, Y1.4; also elsewhere on the board
GPIO28_MCU_IN: R50.2; also elsewhere on the board
LDO15A_1V8: C96.2, C97.2, R48.1, R96.1, R97.1, R99.1; also elsewhere on the board
unnamed: C83.1, R95.2, Y1.3
unnamed: J19.1, TP34.1
unnamed: J19.2, R94.2
unnamed: J19.3, R93.2
unnamed: J19.4, TP33.1
unnamed: Q8.1 (B), R28.1, R47.2
unnamed: Q8.3 (C), R48.2, R50.1
unnamed: C96.1, Q10.1 (B), R96.2
unnamed: C97.1, Q11.1 (B), R99.2
unnamed: TP35.1, U12.4 (GPIO2)
unnamed: TP36.1, U12.5 (GPIO3)
unnamed: TP46.1, U12.15 (GPIO12)
unnamed: TP47.1, U12.16 (GPIO13)
unnamed: TP48.1, U12.17 (GPIO14)
unnamed: TP49.1, U12.18 (GPIO15)
unnamed: C84.1, C85.1, C86.1, U12.23 (DVDD), U12.45 (VREG_VOUT), U12.50 (DVDD)
unnamed: C82.1, U12.20 (XIN), Y1.1
unnamed: R95.1, U12.21 (XOUT)
UART0_RXD: Q10.3 (C), R97.2; also elsewhere on the board
UART0_TXD: Q11.2 (E); also elsewhere on the board
VREG_3V3: C87.1, C88.1, C89.1, C90.1, C91.1, C92.1, C93.1, C94.1, C95.1, IC1.8 (VCC), R92.1, R98.1, U12.1 (IOVDD), U12.10 (IOVDD), U12.22 (IOVDD), U12.33 (IOVDD), U12.42 (IOVDD), U12.43 (ADC_AVDD), U12.44 (VREG_IN), U12.48 (USB_VDD), U12.49 (IOVDD); also elsewhere on the board

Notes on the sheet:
micro-B USB

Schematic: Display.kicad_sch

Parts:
U1: SC206EEMDA-G51-UGNDA; SC200E_SC206E; Part Number SC200EEMNA-E53-UGNDA

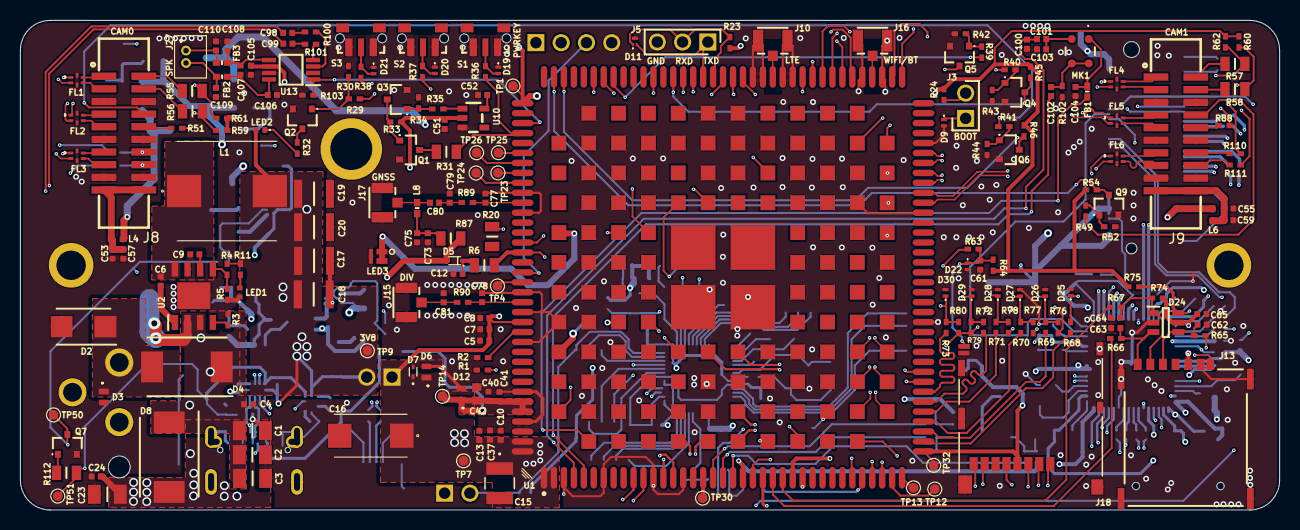
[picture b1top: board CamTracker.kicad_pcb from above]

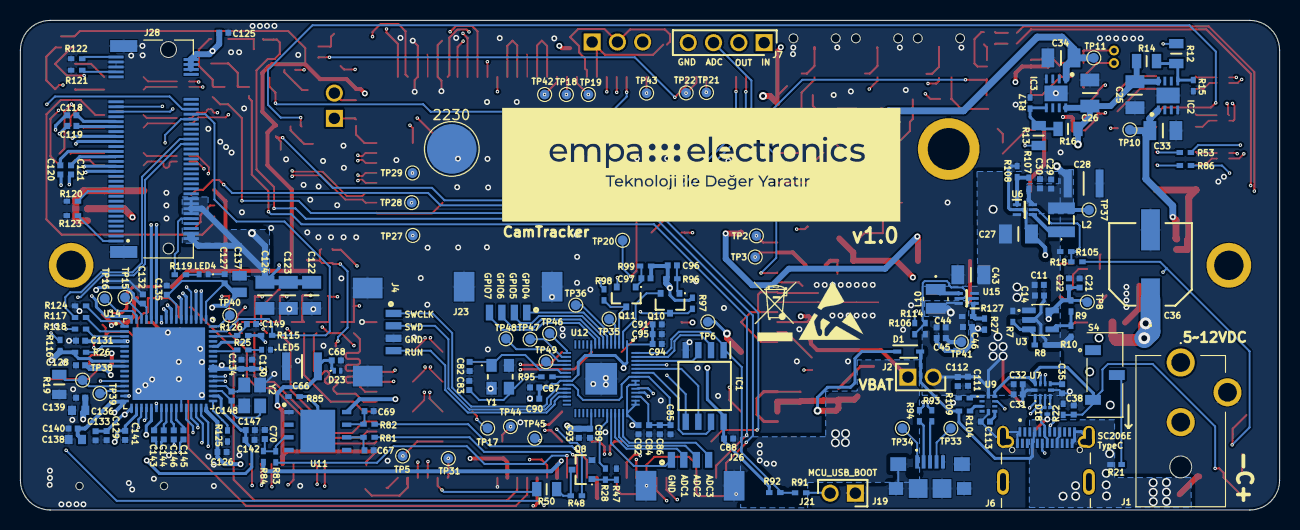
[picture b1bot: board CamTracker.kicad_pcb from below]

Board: 6 copper layers, 126.6 x 49.2 mm, 411 parts (206 on the bottom side), 307 nets.

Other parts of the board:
2230: TestPoint_Pad_D3.0mm
M701, M701#2: M.2 Solder Nut; MountingHole_3mm_Pad
v1.0: LOGO; Logo_EMPA_Official

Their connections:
GND: 2230.1, M701.1, M701#2.1; also elsewhere on the board
